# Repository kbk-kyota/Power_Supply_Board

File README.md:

# Power_Supply_Board
電源供給基盤
構造としては単純で、バッテリーからDCDCコンバータを通じてそれぞれへ電源を供給させるのみ

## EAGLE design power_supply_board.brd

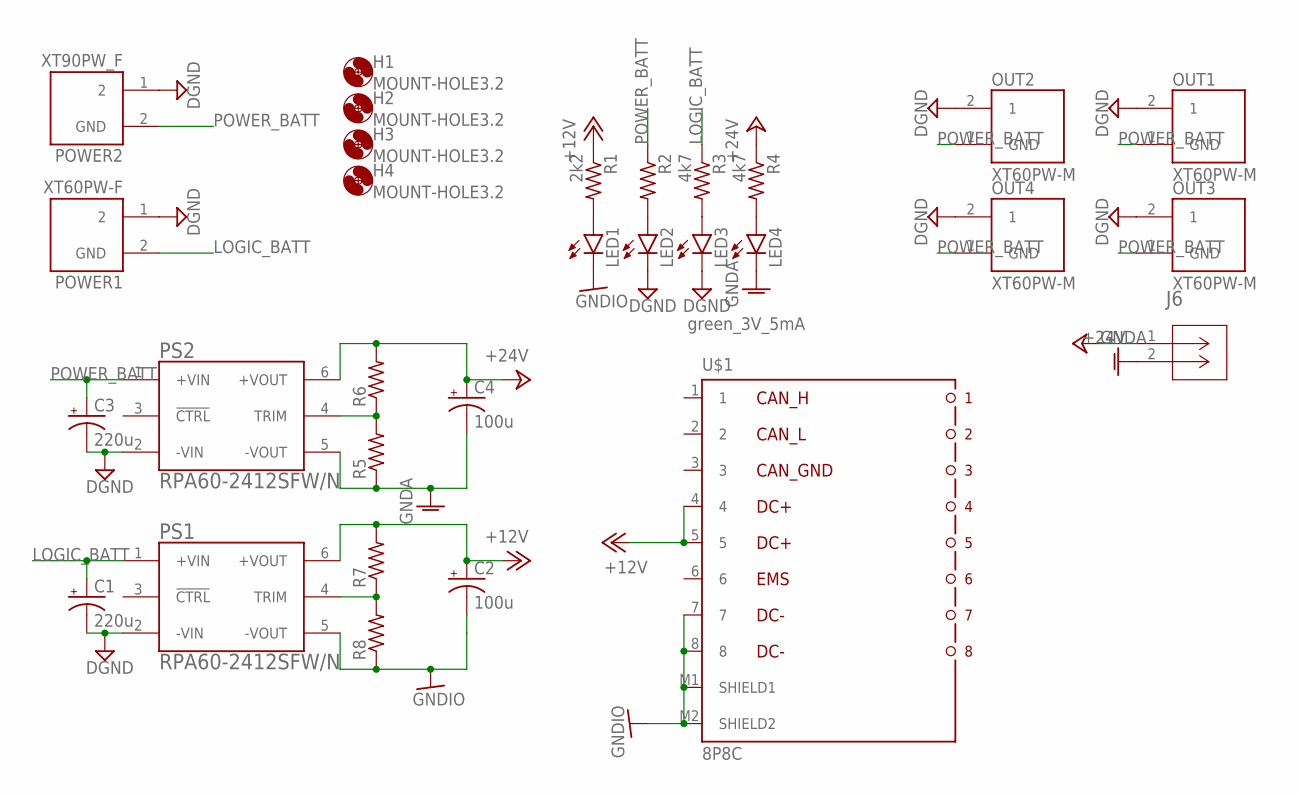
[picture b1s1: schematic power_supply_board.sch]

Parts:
C1, C3: 220u; E2,5-5
C2, C4: 100u; E2-5
H1, H2, H3, H4: MOUNT-HOLE3.2; 3,2
J6: 1744426-2; CONN2_1744426-2
LED1, LED2, LED4: LEDSML0603; SML0603
LED3: green_3V_5mA; SML0603
OUT1, OUT2, OUT3, OUT4: XT60PW-M; AMASS_XT60PW_M
POWER1: XT60PW-F; AMASS_XT60PW-F
POWER2: XT90PW_F; AMASS_XT90PW_F
PS1, PS2: RPA60-2412SFW/N; CONV_RPA60-2412SFW/N
R1: 2k2; R0603
R2, R5, R6, R7, R8: R-US_R0603; R0603
R3, R4: 4k7; R0603
U$1: 8P8C

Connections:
+12V: C2.+, PS1.6 (+VOUT), R1.1, R7.2, U$1.4, U$1.5
+24V: C4.+, J6.1, PS2.6 (+VOUT), R4.1, R6.2
DGND: C1.-, C3.-, LED2.C, LED3.C, OUT1.2 (1), OUT2.2 (1), OUT3.2 (1), OUT4.2 (1), POWER1.1 (2), POWER2.1 (2), PS1.2 (-VIN), PS2.2 (-VIN)
GNDA: C4.-, J6.2, LED4.C, PS2.5 (-VOUT), R5.1
GNDIO: C2.-, LED1.C, PS1.5 (-VOUT), R8.1, U$1.7, U$1.8, U$1.M1 (SHIELD1), U$1.M2 (SHIELD2)
LOGIC_BATT: C1.+, POWER1.2 (GND), PS1.1 (+VIN), R3.1
unnamed: LED1.A, R1.2
unnamed: LED2.A, R2.2
unnamed: LED3.A, R3.2
unnamed: LED4.A, R4.2
unnamed: PS2.4 (TRIM), R5.2, R6.1
unnamed: PS1.4 (TRIM), R7.1, R8.2
POWER_BATT: C3.+, OUT1.1 (GND), OUT2.1 (GND), OUT3.1 (GND), OUT4.1 (GND), POWER2.2 (GND), PS2.1 (+VIN), R2.1

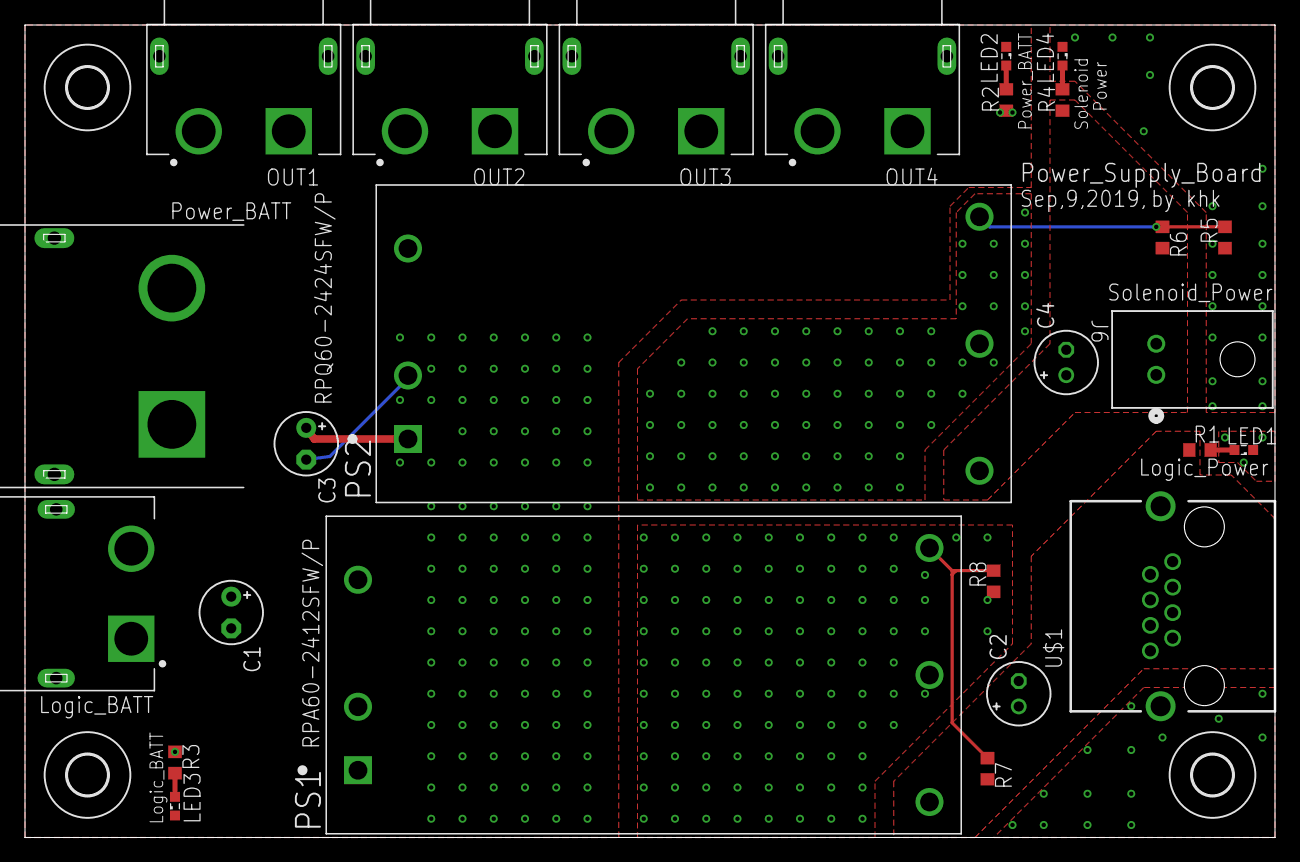
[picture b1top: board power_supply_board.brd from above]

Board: 2 copper layers, 100.0 x 65.0 mm, 30 parts (0 on the bottom side), 13 nets.

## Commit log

2019-08-11 xtコネクタのサーマルが外れていない問題を修正
2019-09-01 xt及びコンバータのthermalを外した
2019-09-07 ガーバーファイルを追加
2019-09-08 ベタの一部を修正
2020-01-08 配線ミスを修正
